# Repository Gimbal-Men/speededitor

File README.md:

One-Handed DaVinci Resolve Hackpad
This project is a one-handed hackpad designed specifically to improve the video editing workflow in DaVinci Resolve, with a strong focus on the Cut Page and Edit Page.

Input Layout & Functions:
The hackpad consists of 12 mechanical keys and 2 rotary encoders.

Undo	
Previous Cut
Next Cut
Up Track
Down Track
In/Out
Cut
Ripple Delete
Append

Encoder 1 (Jog / Playback):

Rotate: Move timeline (coarse)

Press: Play / Pause

Press + Rotate: Move timeline (fine)

Encoder 2 (Timeline / Clip):

Rotate: Timeline zoom

Press: Select clip

Press + Rotate: Move selected clip

Schematic:

PCB Design:

Case Design:

Materials:
Seeed XIAO RP2040	1x
MX-style mechanical switches 12x
EC11 rotary encoders	2x
1N4148 diodes (through-hole) 12x
Blank DSA keycaps	12x
M3x16mm screws	4x
M3 heatset inserts	4x
3D printed case parts	1 set

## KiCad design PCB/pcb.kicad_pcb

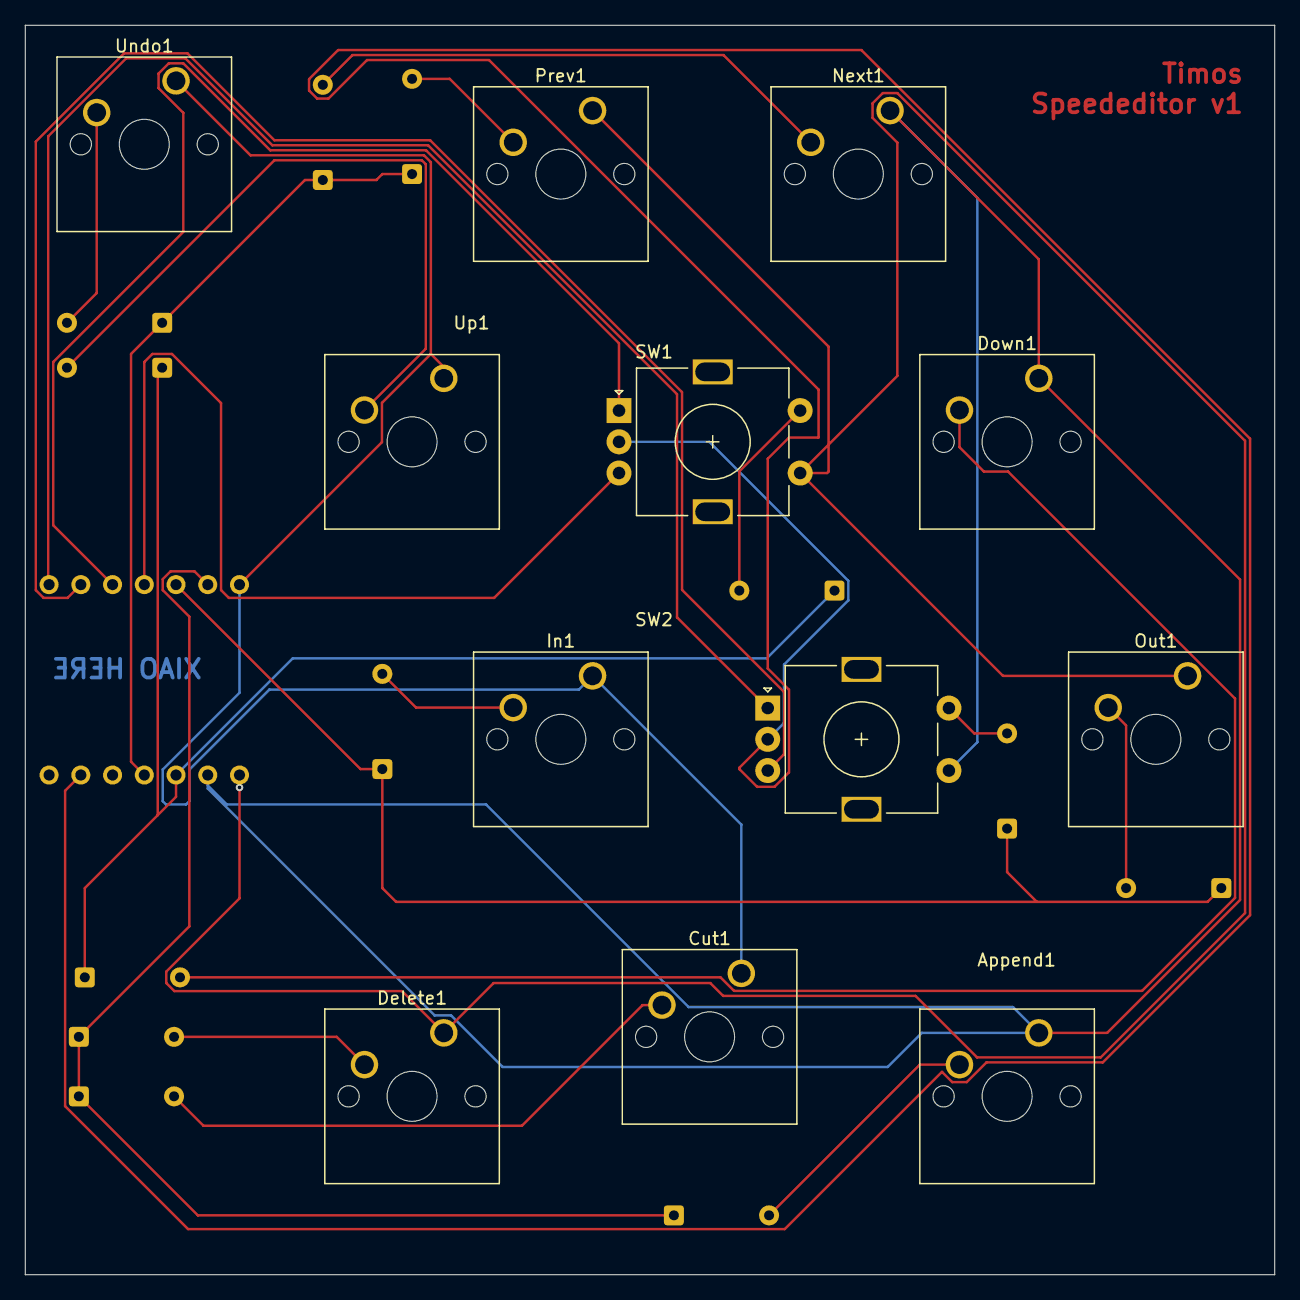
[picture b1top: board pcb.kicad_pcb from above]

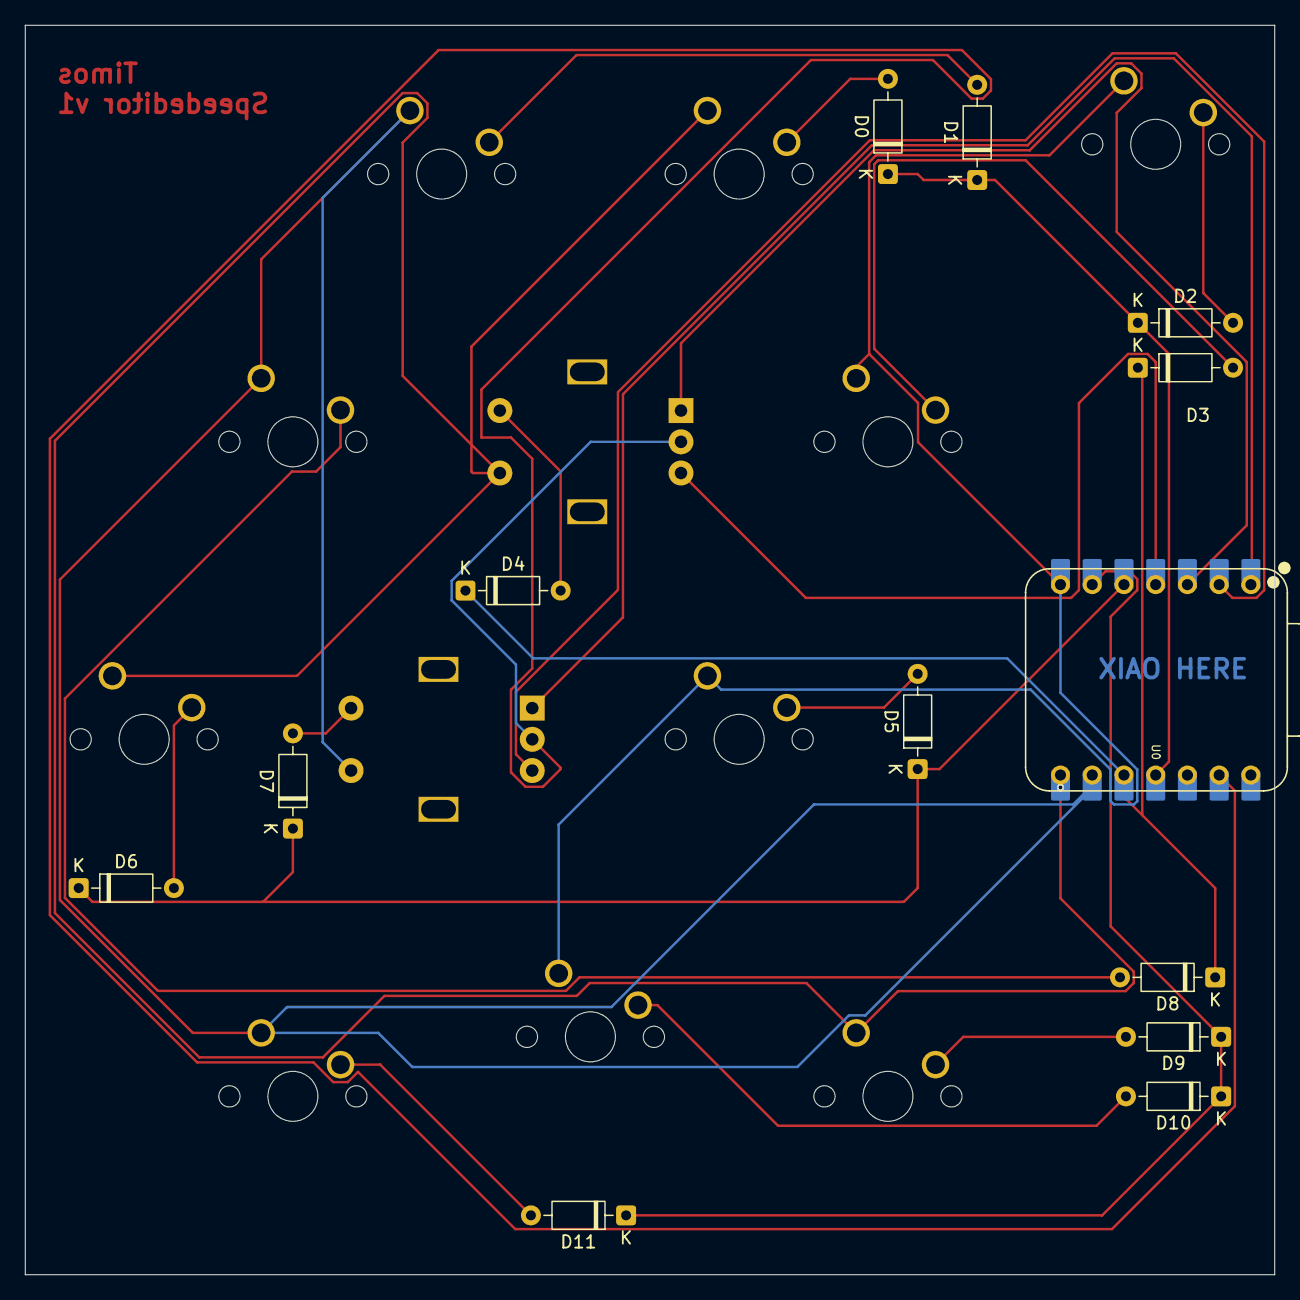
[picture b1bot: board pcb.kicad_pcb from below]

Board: 2 copper layers, 100.0 x 100.0 mm, 25 parts (13 on the bottom side), 24 nets.

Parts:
Append1: SW_Push; SW_Cherry_MX_1.00u_PCB
Cut1: SW_Push; SW_Cherry_MX_1.00u_PCB
D0, D1, D2, D3, D4, D5, D6, D7, D8, D9, D10, D11: 1N4148; D_DO-35_SOD27_P7.62mm_Horizontal
Delete1: SW_Push; SW_Cherry_MX_1.00u_PCB
Down1: SW_Push; SW_Cherry_MX_1.00u_PCB
In1: SW_Push; SW_Cherry_MX_1.00u_PCB
Next1: SW_Push; SW_Cherry_MX_1.00u_PCB
Out1: SW_Push; SW_Cherry_MX_1.00u_PCB
Prev1: SW_Push; SW_Cherry_MX_1.00u_PCB
SW1: Jog; RotaryEncoder_Alps_EC11E-Switch_Vertical_H20mm
SW2: ENC 2; RotaryEncoder_Alps_EC11E-Switch_Vertical_H20mm
U0: XIAO-RP2040-DIP
Undo1: SW_Push; SW_Cherry_MX_1.00u_PCB
Up1: SW_Push; SW_Cherry_MX_1.00u_PCB

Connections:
/COL0: Cut1.1, In1.1, U0.7 (GPIO0/TX), Undo1.1, Up1.1
/COL1: Delete1.1, Out1.1, Prev1.1, SW1.S1, U0.8 (GPIO1/RX)
/COL2: Append1.1, Down1.1, Next1.1, SW2.S1, U0.9 (GPIO2/SCK)
/ROW0: D0.1 (K), D1.1 (K), D2.1 (K), U0.11 (GPIO3/MOSI)
/ROW1: D3.1 (K), D4.1 (K), D8.1 (K), U0.10 (GPIO4/MISO)
/ROW2: D5.1 (K), D6.1 (K), D7.1 (K), U0.5 (GPIO6/SDA)
/ROW3: D9.1 (K), D10.1 (K), D11.1 (K), U0.6 (GPIO7/SCL)
GND: SW1.C, SW2.C, U0.13 (GND)
unnamed: D2.2 (A), Undo1.2
unnamed: D3.2 (A), Up1.2
unnamed: D5.2 (A), In1.2
unnamed: Cut1.2, D10.2 (A)
unnamed: D0.2 (A), Prev1.2
unnamed: D4.2 (A), SW1.S2
unnamed: D6.2 (A), Out1.2
unnamed: D9.2 (A), Delete1.2
unnamed: D1.2 (A), Next1.2
unnamed: D8.2 (A), Down1.2
unnamed: D7.2 (A), SW2.S2
unnamed: Append1.2, D11.2 (A)
unnamed: SW2.A, U0.1 (GPIO26/ADC0/A0)
unnamed: SW2.B, U0.2 (GPIO27/ADC1/A1)
unnamed: SW1.A, U0.3 (GPIO28/ADC2/A2)
unnamed: SW1.B, U0.4 (GPIO29/ADC3/A3)
